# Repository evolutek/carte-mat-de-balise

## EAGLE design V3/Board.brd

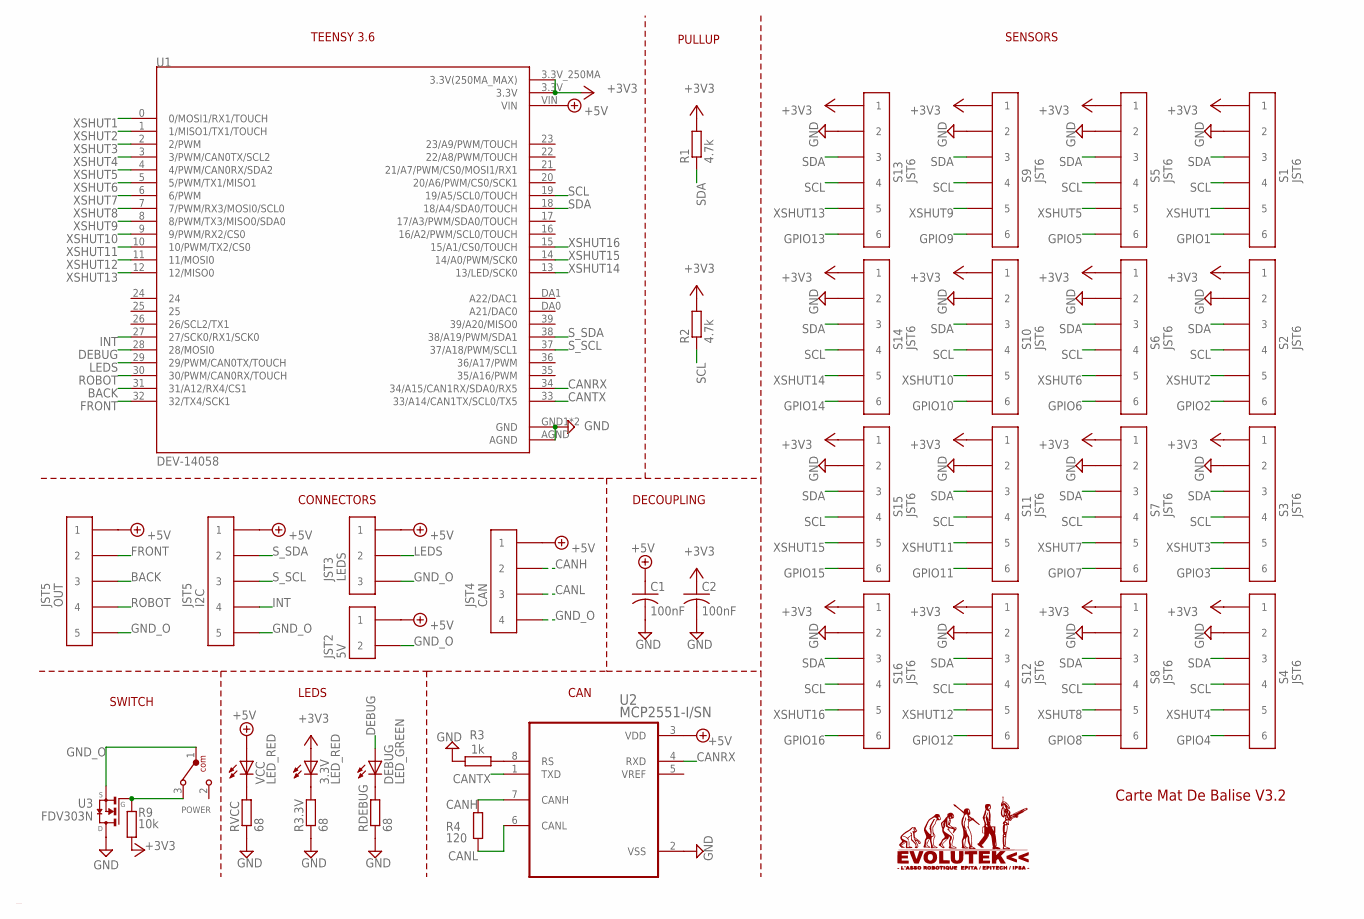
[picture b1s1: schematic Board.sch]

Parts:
3.3V: LED_RED; CHIPLED_0805
5V: JST2; B02B-PASK
C1, C2: 100nF; C0603
CAN: JST4; B04B-PASK
DEBUG: LED_GREEN; CHIPLED_0805
I2C: JST5; B05B-PASK
LEDS: JST3; B03B-PASK
OUT: JST5; B05B-PASK
POWER: 450302014072
R1, R2: 4.7k; R0603
R3: 1k; R0603
R3.3V: 68; R0603
R4: 120; R0603
R9: 10k; R0603
RDEBUG: 68; R0603
RVCC: 68; R0603
S1, S2, S3, S4, S5, S6, S7, S8, S9, S10, S11, S12, S13, S14, S15, S16: JST6; B06B-PASK
U1: DEV-14058; MODULE_DEV-14058
U2: MCP2551-I/SN; SOIC127P599X175-8N
U3: FDV303N; SOT23
VCC: LED_RED; CHIPLED_0805

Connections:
+3V3: 3.3V.A, C2.1, R1.2, R2.2, R9.2, S1.P$1 (1), S2.P$1 (1), S3.P$1 (1), S4.P$1 (1), S5.P$1 (1), S6.P$1 (1), S7.P$1 (1), S8.P$1 (1), S9.P$1 (1), S10.P$1 (1), S11.P$1 (1), S12.P$1 (1), S13.P$1 (1), S14.P$1 (1), S15.P$1 (1), S16.P$1 (1), U1.3.3V, U1.3.3V_250MA (3.3V(250MA_MAX))
+5V: 5V.P$1 (1), C1.1, CAN.P$1 (1), I2C.P$1 (1), LEDS.P$1 (1), OUT.P$1 (1), U1.VIN, U2.3 (VDD), VCC.A
BACK: OUT.P$3 (3), U1.31 (31/A12/RX4/CS1)
CANH: CAN.P$2 (2), R4.1, U2.7 (CANH)
CANL: CAN.P$3 (3), R4.2, U2.6 (CANL)
CANRX: U1.34 (34/A15/CAN1RX/SDA0/RX5), U2.4 (RXD)
CANTX: U1.33 (33/A14/CAN1TX/SCL0/TX5), U2.1 (TXD)
DEBUG: DEBUG.A, U1.28 (28/MOSI0)
FRONT: OUT.P$2 (2), U1.32 (32/TX4/SCK1)
GND: C1.2, C2.2, R3.2, R3.3V.1, RDEBUG.1, RVCC.1, S1.P$2 (2), S2.P$2 (2), S3.P$2 (2), S4.P$2 (2), S5.P$2 (2), S6.P$2 (2), S7.P$2 (2), S8.P$2 (2), S9.P$2 (2), S10.P$2 (2), S11.P$2 (2), S12.P$2 (2), S13.P$2 (2), S14.P$2 (2), S15.P$2 (2), S16.P$2 (2), U1.AGND, U1.GND1 (GND), U1.GND2 (GND), U2.2 (VSS), U3.3 (D)
GND_O: 5V.P$2 (2), CAN.P$4 (4), I2C.P$5 (5), LEDS.P$3 (3), OUT.P$5 (5), POWER.1, U3.2 (S)
GPIO1: S1.P$6 (6)
GPIO2: S2.P$6 (6)
GPIO3: S3.P$6 (6)
GPIO4: S4.P$6 (6)
GPIO5: S5.P$6 (6)
GPIO6: S6.P$6 (6)
GPIO7: S7.P$6 (6)
GPIO8: S8.P$6 (6)
GPIO9: S9.P$6 (6)
GPIO10: S10.P$6 (6)
GPIO11: S11.P$6 (6)
GPIO12: S12.P$6 (6)
GPIO13: S13.P$6 (6)
GPIO14: S14.P$6 (6)
GPIO15: S15.P$6 (6)
GPIO16: S16.P$6 (6)
INT: I2C.P$4 (4), U1.27 (27/SCK0/RX1/SCK0)
LEDS: LEDS.P$2 (2), U1.29 (29/PWM/CAN0TX/TOUCH)
unnamed: 3.3V.C, R3.3V.2
unnamed: DEBUG.C, RDEBUG.2
unnamed: R3.1, U2.8 (RS)
unnamed: RVCC.2, VCC.C
unnamed: POWER.3, R9.1, U3.1 (G)
ROBOT: OUT.P$4 (4), U1.30 (30/PWM/CAN0RX/TOUCH)
SCL: R2.1, S1.P$4 (4), S2.P$4 (4), S3.P$4 (4), S4.P$4 (4), S5.P$4 (4), S6.P$4 (4), S7.P$4 (4), S8.P$4 (4), S9.P$4 (4), S10.P$4 (4), S11.P$4 (4), S12.P$4 (4), S13.P$4 (4), S14.P$4 (4), S15.P$4 (4), S16.P$4 (4), U1.19 (19/A5/SCL0/TOUCH)
SDA: R1.1, S1.P$3 (3), S2.P$3 (3), S3.P$3 (3), S4.P$3 (3), S5.P$3 (3), S6.P$3 (3), S7.P$3 (3), S8.P$3 (3), S9.P$3 (3), S10.P$3 (3), S11.P$3 (3), S12.P$3 (3), S13.P$3 (3), S14.P$3 (3), S15.P$3 (3), S16.P$3 (3), U1.18 (18/A4/SDA0/TOUCH)
S_SCL: I2C.P$3 (3), U1.37 (37/A18/PWM/SCL1)
S_SDA: I2C.P$2 (2), U1.38 (38/A19/PWM/SDA1)
XSHUT1: S1.P$5 (5), U1.0 (0/MOSI1/RX1/TOUCH)
XSHUT2: S2.P$5 (5), U1.1 (1/MISO1/TX1/TOUCH)
XSHUT3: S3.P$5 (5), U1.2 (2/PWM)
XSHUT4: S4.P$5 (5), U1.3 (3/PWM/CAN0TX/SCL2)
XSHUT5: S5.P$5 (5), U1.4 (4/PWM/CAN0RX/SDA2)
XSHUT6: S6.P$5 (5), U1.5 (5/PWM/TX1/MISO1)
XSHUT7: S7.P$5 (5), U1.6 (6/PWM)
XSHUT8: S8.P$5 (5), U1.7 (7/PWM/RX3/MOSI0/SCL0)
XSHUT9: S9.P$5 (5), U1.8 (8/PWM/TX3/MISO0/SDA0)
XSHUT10: S10.P$5 (5), U1.9 (9/PWM/RX2/CS0)
XSHUT11: S11.P$5 (5), U1.10 (10/PWM/TX2/CS0)
XSHUT12: S12.P$5 (5), U1.11 (11/MOSI0)
XSHUT13: S13.P$5 (5), U1.12 (12/MISO0)
XSHUT14: S14.P$5 (5), U1.13 (13/LED/SCK0)
XSHUT15: S15.P$5 (5), U1.14 (14/A0/PWM/SCK0)
XSHUT16: S16.P$5 (5), U1.15 (15/A1/CS0/TOUCH)

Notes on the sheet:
SENSORS
TEENSY 3.6
CONNECTORS
SWITCH
DECOUPLING
LEDS
PULLUP
CAN
C:/Users/coren/Documents/MEGA/logo_evo.bmp
Carte Mat De Balise V3.2

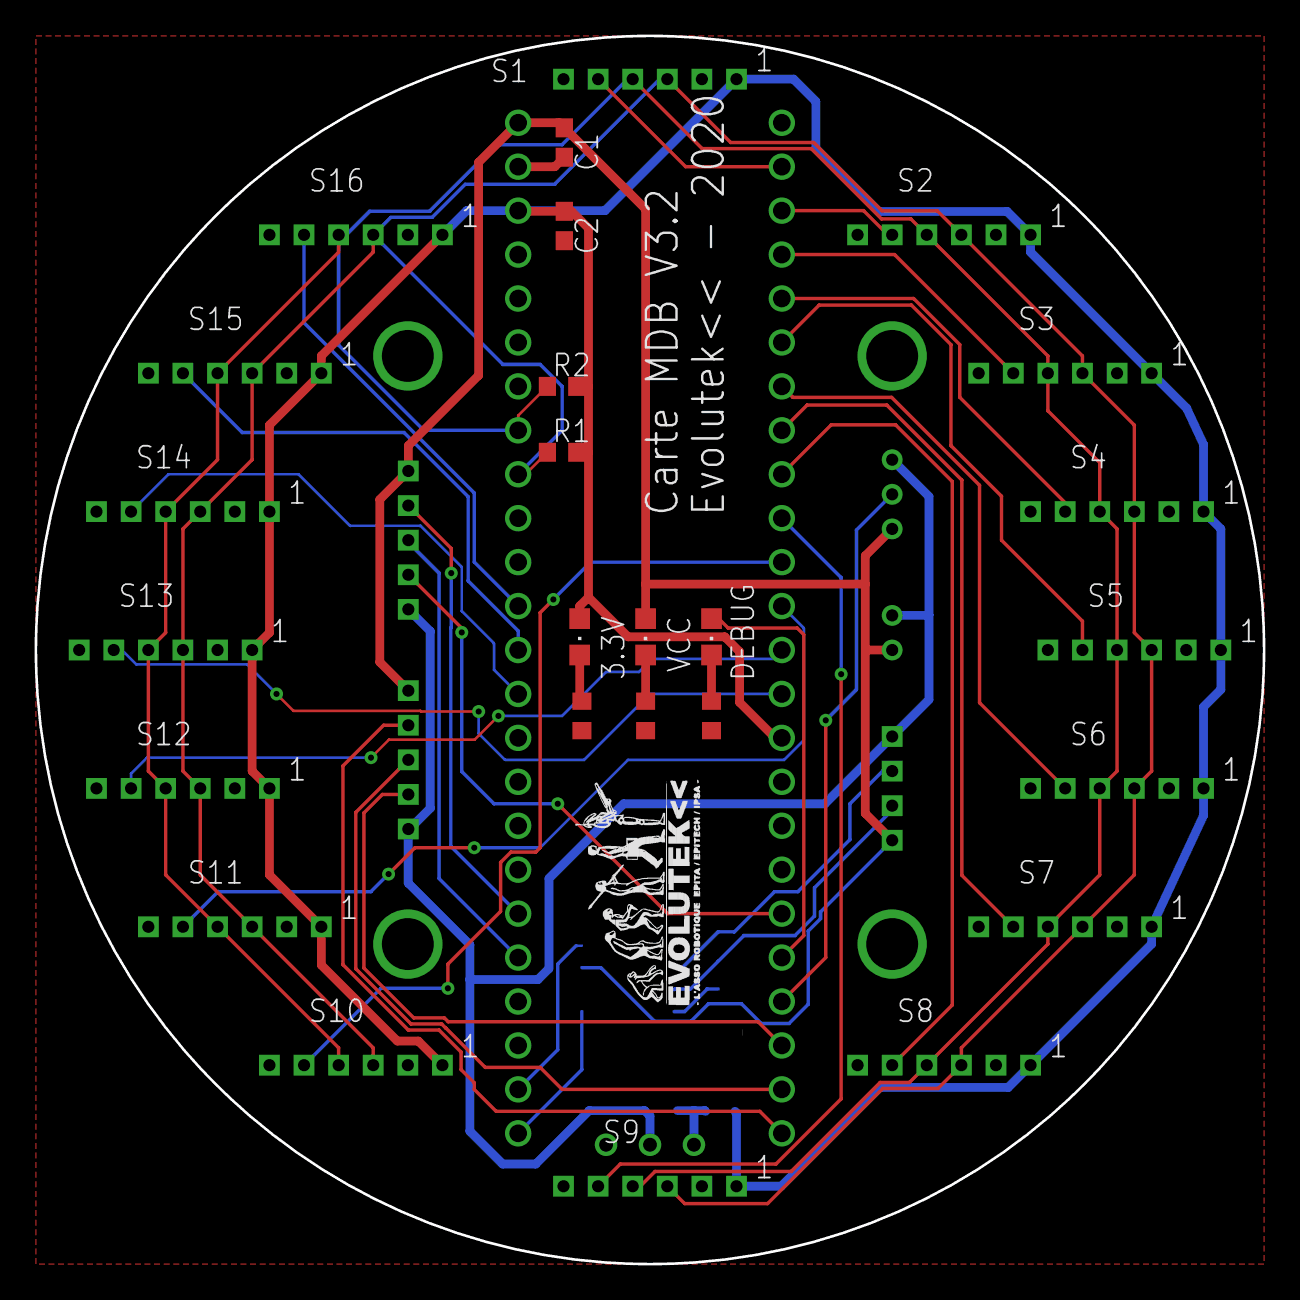
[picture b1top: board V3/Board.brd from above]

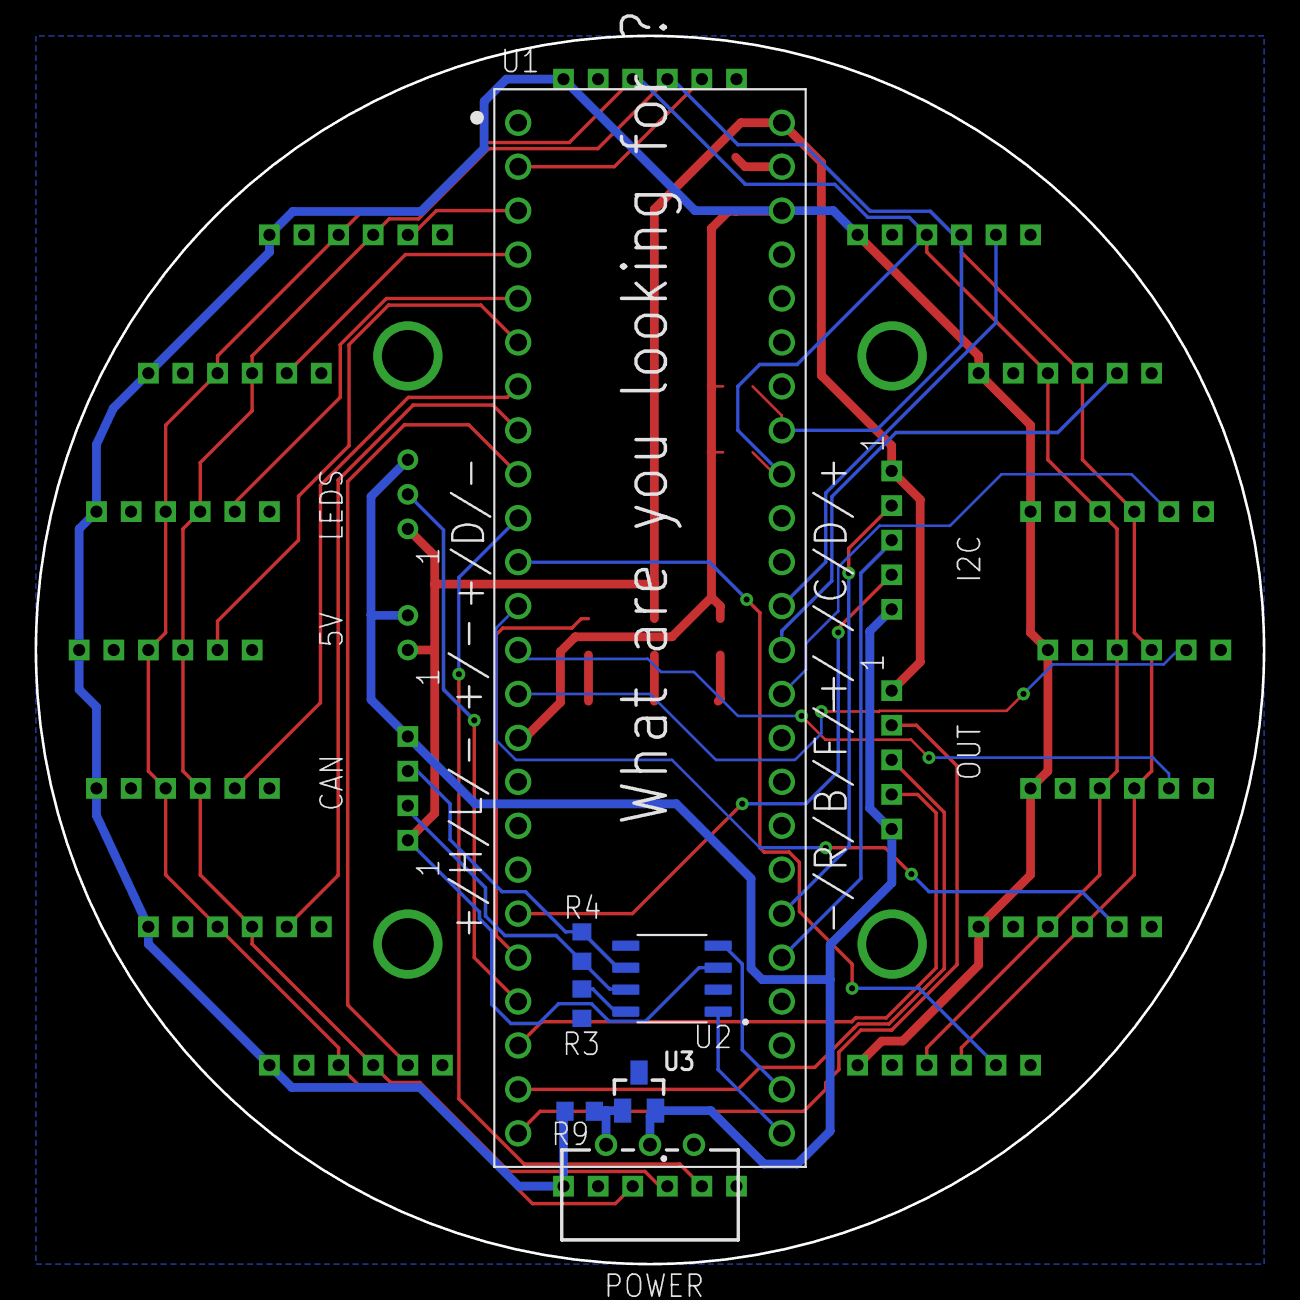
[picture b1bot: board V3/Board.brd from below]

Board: 2 copper layers, 71.0 x 71.0 mm, 38 parts (12 on the bottom side), 39 nets.

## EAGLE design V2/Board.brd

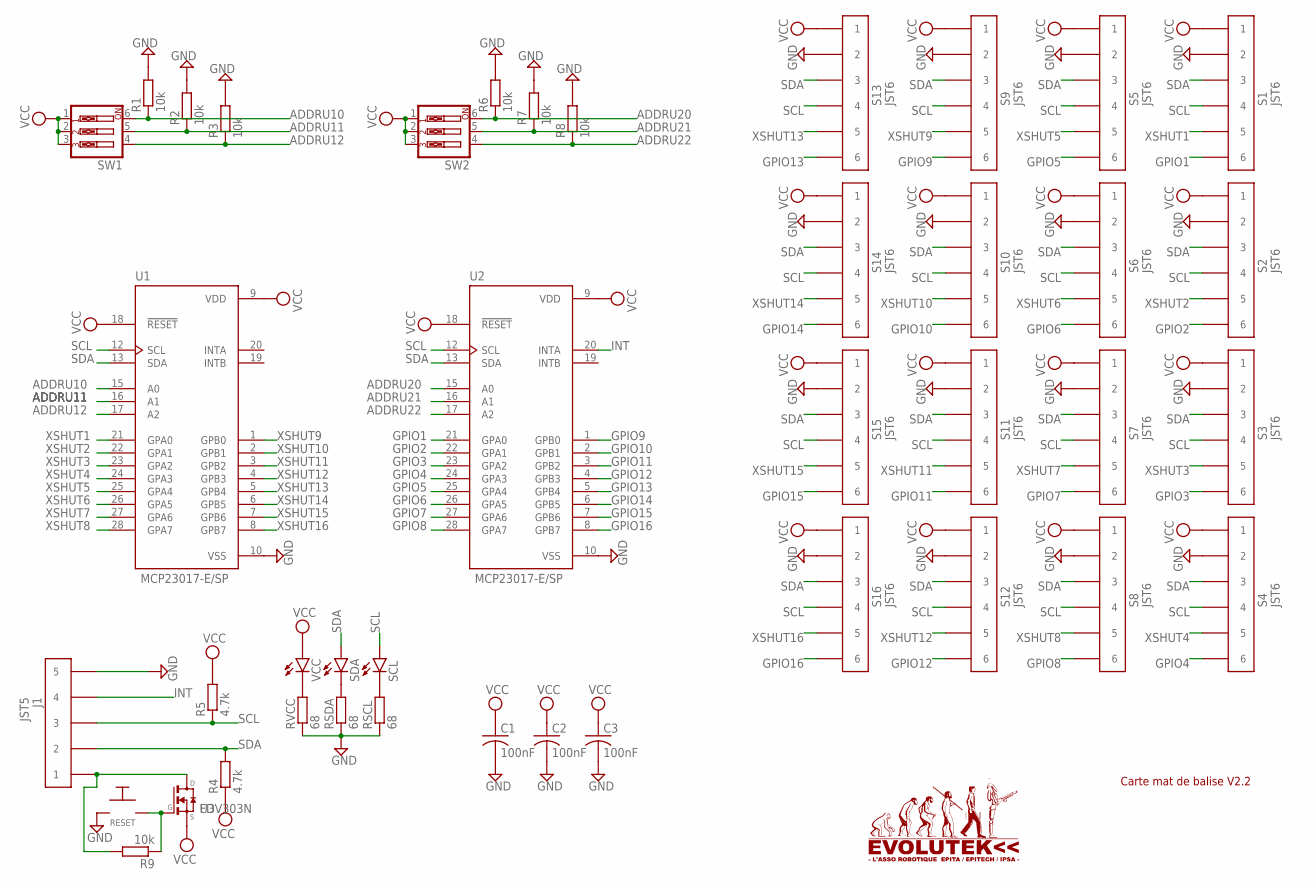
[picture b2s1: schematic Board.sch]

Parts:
C1, C2, C3: 100nF; C0603
J1: JST5; B05B-PASK
R1, R2, R3, R6, R7, R8, R9: 10k; R0603
R4, R5: 4.7k; R0603
RESET: 1825095-3
RSCL: 68; R0603
RSDA: 68; R0603
RVCC: 68; R0603
S1, S2, S3, S4, S5, S6, S7, S8, S9, S10, S11, S12, S13, S14, S15, S16: JST6; B06B-PASK
SCL: LEDCHIPLED_0805; CHIPLED_0805
SDA: LEDCHIPLED_0805; CHIPLED_0805
SW1, SW2: SW_DIP-3; EDG-03
U1, U2: MCP23017-E/SP; DIP787W45P254L3556H508Q28
U3: FDV303N; SOT23
VCC: LEDCHIPLED_0805; CHIPLED_0805

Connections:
ADDRU10: R1.1, SW1.6, U1.15 (A0)
ADDRU11: R2.1, SW1.5, U1.16 (A1)
ADDRU12: R3.1, SW1.4, U1.17 (A2)
ADDRU20: R6.1, SW2.6, U2.15 (A0)
ADDRU21: R7.1, SW2.5, U2.16 (A1)
ADDRU22: R8.1, SW2.4, U2.17 (A2)
GND: C1.2, C2.2, C3.2, J1.P$5 (5), R1.2, R2.2, R3.2, R6.2, R7.2, R8.2, RESET.P$3, RSCL.1, RSDA.1, RVCC.1, S1.P$2 (2), S2.P$2 (2), S3.P$2 (2), S4.P$2 (2), S5.P$2 (2), S6.P$2 (2), S7.P$2 (2), S8.P$2 (2), S9.P$2 (2), S10.P$2 (2), S11.P$2 (2), S12.P$2 (2), S13.P$2 (2), S14.P$2 (2), S15.P$2 (2), S16.P$2 (2), U1.10 (VSS), U2.10 (VSS)
GPIO1: S1.P$6 (6), U2.21 (GPA0)
GPIO2: S2.P$6 (6), U2.22 (GPA1)
GPIO3: S3.P$6 (6), U2.23 (GPA2)
GPIO4: S4.P$6 (6), U2.24 (GPA3)
GPIO5: S5.P$6 (6), U2.25 (GPA4)
GPIO6: S6.P$6 (6), U2.26 (GPA5)
GPIO7: S7.P$6 (6), U2.27 (GPA6)
GPIO8: S8.P$6 (6), U2.28 (GPA7)
GPIO9: S9.P$6 (6), U2.1 (GPB0)
GPIO10: S10.P$6 (6), U2.2 (GPB1)
GPIO11: S11.P$6 (6), U2.3 (GPB2)
GPIO12: S12.P$6 (6), U2.4 (GPB3)
GPIO13: S13.P$6 (6), U2.5 (GPB4)
GPIO14: S14.P$6 (6), U2.6 (GPB5)
GPIO15: S15.P$6 (6), U2.7 (GPB6)
GPIO16: S16.P$6 (6), U2.8 (GPB7)
INT: J1.P$4 (4), U2.20 (INTA)
unnamed: R9.1, RESET.P$1, U3.1 (G)
unnamed: J1.P$1 (1), R9.2, U3.3 (D)
unnamed: RSDA.2, SDA.C
unnamed: RSCL.2, SCL.C
unnamed: RVCC.2, VCC.C
SCL: J1.P$3 (3), R5.1, S1.P$4 (4), S2.P$4 (4), S3.P$4 (4), S4.P$4 (4), S5.P$4 (4), S6.P$4 (4), S7.P$4 (4), S8.P$4 (4), S9.P$4 (4), S10.P$4 (4), S11.P$4 (4), S12.P$4 (4), S13.P$4 (4), S14.P$4 (4), S15.P$4 (4), S16.P$4 (4), SCL.A, U1.12 (SCL), U2.12 (SCL)
SDA: J1.P$2 (2), R4.2, S1.P$3 (3), S2.P$3 (3), S3.P$3 (3), S4.P$3 (3), S5.P$3 (3), S6.P$3 (3), S7.P$3 (3), S8.P$3 (3), S9.P$3 (3), S10.P$3 (3), S11.P$3 (3), S12.P$3 (3), S13.P$3 (3), S14.P$3 (3), S15.P$3 (3), S16.P$3 (3), SDA.A, U1.13 (SDA), U2.13 (SDA)
VCC: C1.1, C2.1, C3.1, R4.1, R5.2, S1.P$1 (1), S2.P$1 (1), S3.P$1 (1), S4.P$1 (1), S5.P$1 (1), S6.P$1 (1), S7.P$1 (1), S8.P$1 (1), S9.P$1 (1), S10.P$1 (1), S11.P$1 (1), S12.P$1 (1), S13.P$1 (1), S14.P$1 (1), S15.P$1 (1), S16.P$1 (1), SW1.1, SW1.2, SW1.3, SW2.1, SW2.2, SW2.3, U1.9 (VDD), U1.18 (!RESET), U2.9 (VDD), U2.18 (!RESET), U3.2 (S), VCC.A
XSHUT1: S1.P$5 (5), U1.21 (GPA0)
XSHUT2: S2.P$5 (5), U1.22 (GPA1)
XSHUT3: S3.P$5 (5), U1.23 (GPA2)
XSHUT4: S4.P$5 (5), U1.24 (GPA3)
XSHUT5: S5.P$5 (5), U1.25 (GPA4)
XSHUT6: S6.P$5 (5), U1.26 (GPA5)
XSHUT7: S7.P$5 (5), U1.27 (GPA6)
XSHUT8: S8.P$5 (5), U1.28 (GPA7)
XSHUT9: S9.P$5 (5), U1.1 (GPB0)
XSHUT10: S10.P$5 (5), U1.2 (GPB1)
XSHUT11: S11.P$5 (5), U1.3 (GPB2)
XSHUT12: S12.P$5 (5), U1.4 (GPB3)
XSHUT13: S13.P$5 (5), U1.5 (GPB4)
XSHUT14: S14.P$5 (5), U1.6 (GPB5)
XSHUT15: S15.P$5 (5), U1.7 (GPB6)
XSHUT16: S16.P$5 (5), U1.8 (GPB7)

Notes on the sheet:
Carte mat de balise V2.2

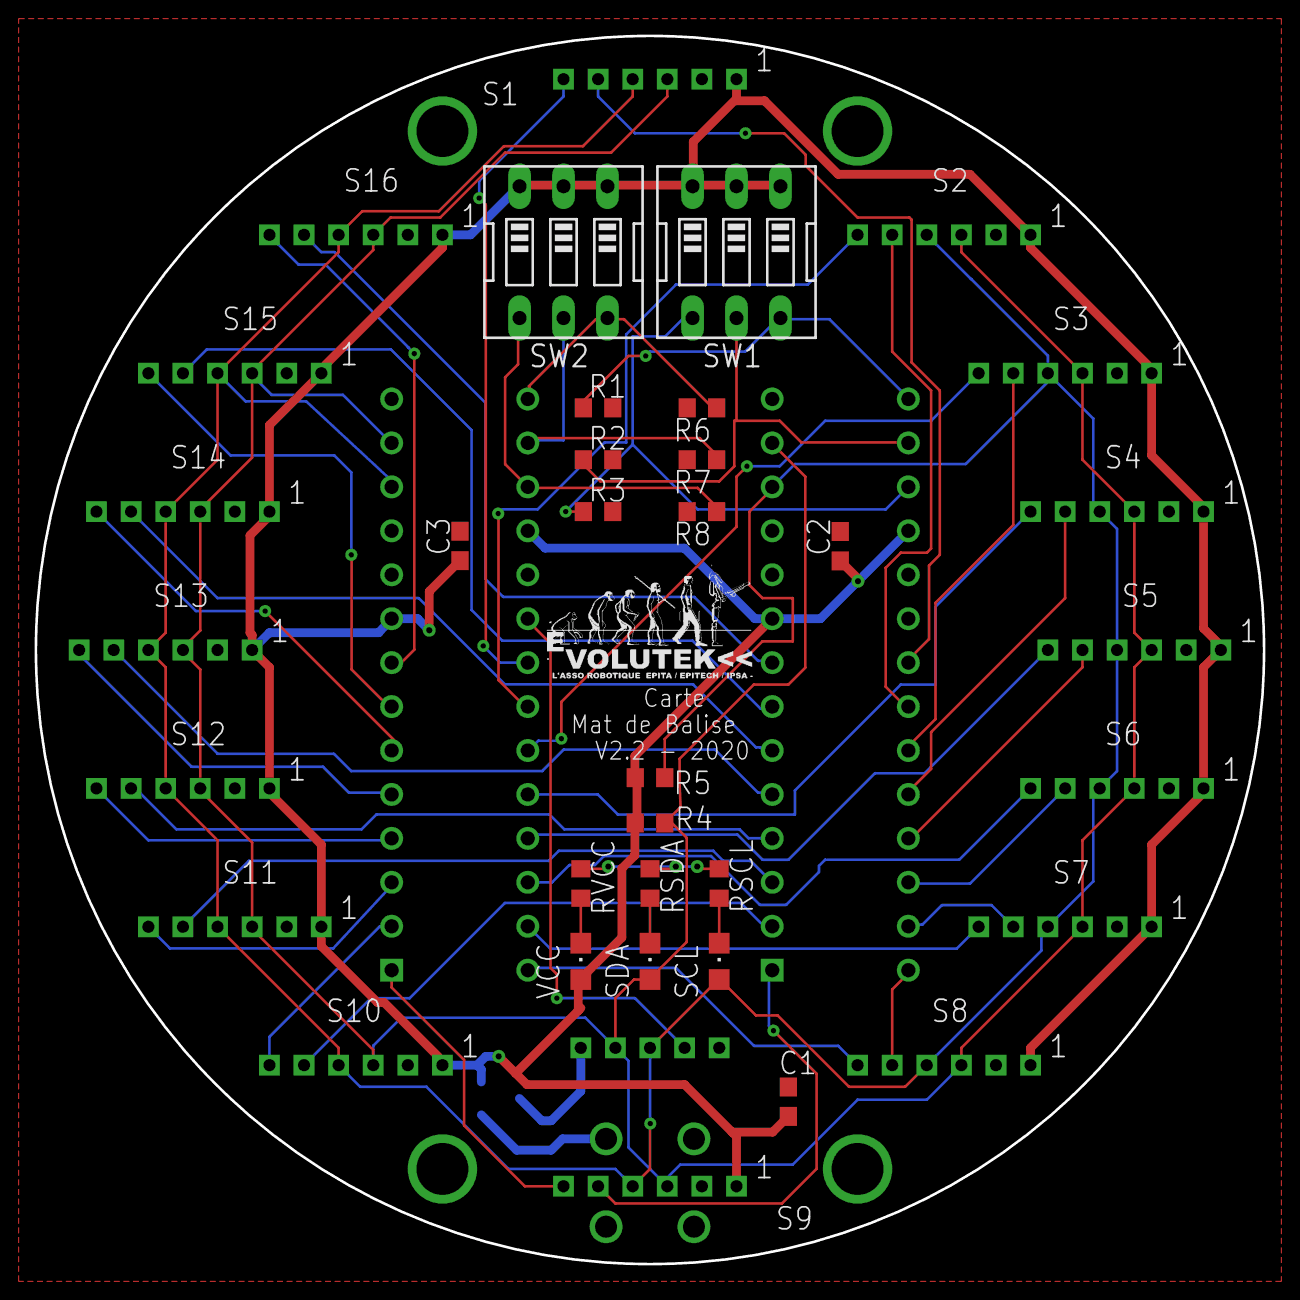
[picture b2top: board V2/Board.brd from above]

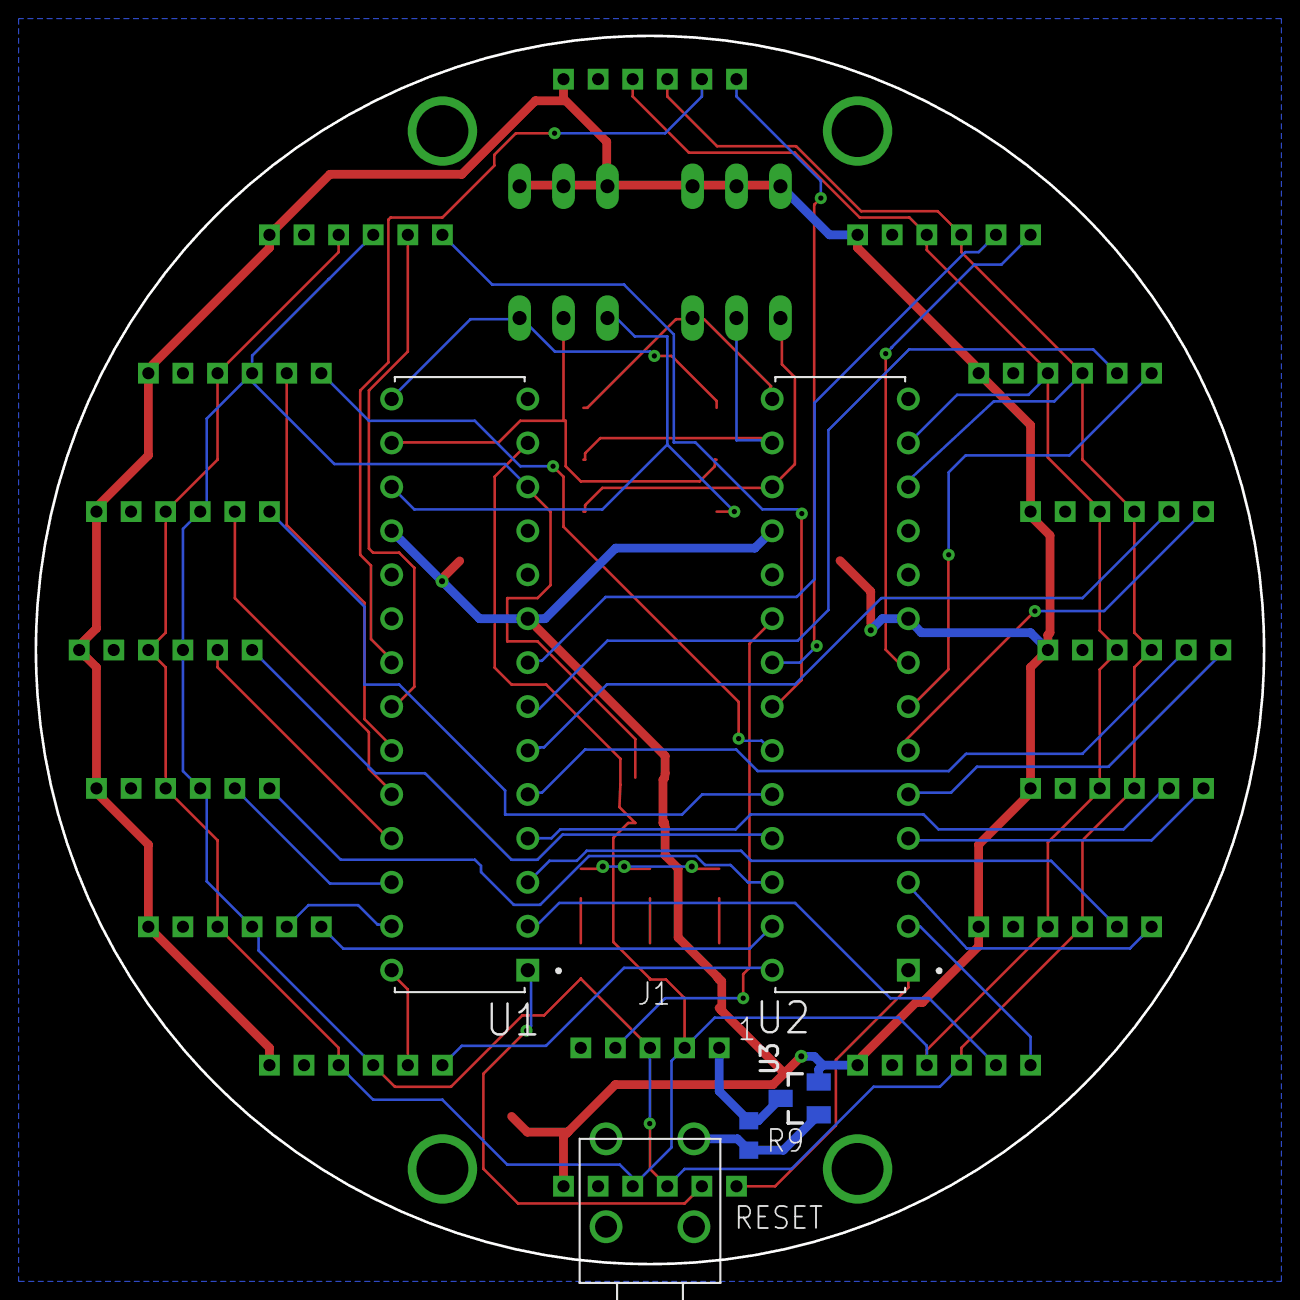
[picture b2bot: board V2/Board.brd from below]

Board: 2 copper layers, 71.0 x 71.0 mm, 41 parts (6 on the bottom side), 48 nets.

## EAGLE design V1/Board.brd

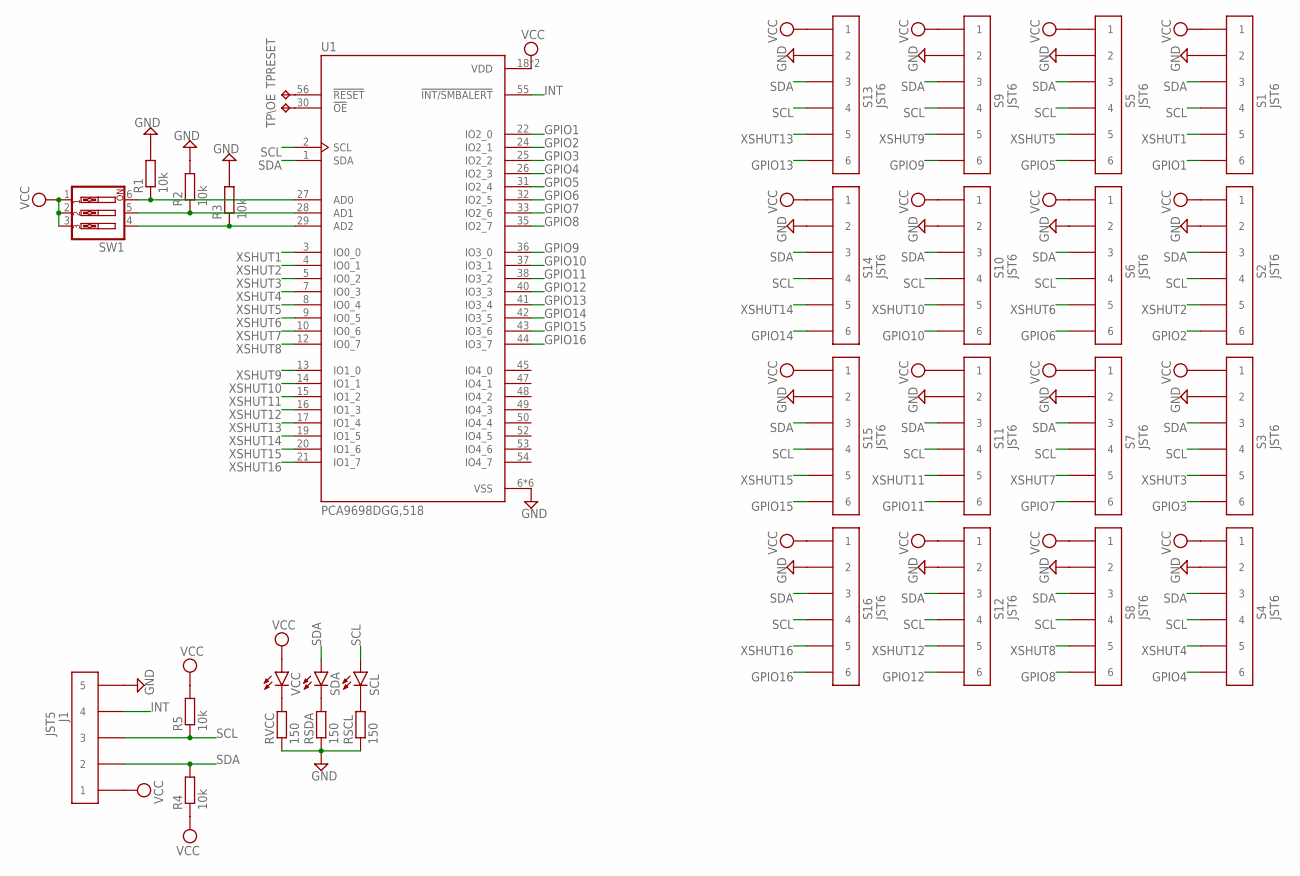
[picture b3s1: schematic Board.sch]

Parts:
J1: JST5; B05B-PASK
R1, R2, R3, R4, R5: 10k; R0603
RSCL: 150; R0603
RSDA: 150; R0603
RVCC: 150; R0603
S1, S2, S3, S4, S5, S6, S7, S8, S9, S10, S11, S12, S13, S14, S15, S16: JST6; B06B-PASK
SCL: LEDCHIPLED_0805; CHIPLED_0805
SDA: LEDCHIPLED_0805; CHIPLED_0805
SW1: SW_DIP-3; EDG-03
TPRESET: TPPAD1-13; P1-13
TP\OE: TPPAD1-13; P1-13
U1: PCA9698DGG,518; SOP50P810X120-56N
VCC: LEDCHIPLED_0805; CHIPLED_0805

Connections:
GND: J1.P$5 (5), R1.2, R2.2, R3.2, RSCL.1, RSDA.1, RVCC.1, S1.P$2 (2), S2.P$2 (2), S3.P$2 (2), S4.P$2 (2), S5.P$2 (2), S6.P$2 (2), S7.P$2 (2), S8.P$2 (2), S9.P$2 (2), S10.P$2 (2), S11.P$2 (2), S12.P$2 (2), S13.P$2 (2), S14.P$2 (2), S15.P$2 (2), S16.P$2 (2), U1.6 (VSS), U1.11 (VSS), U1.23 (VSS), U1.34 (VSS), U1.39 (VSS), U1.51 (VSS)
GPIO1: S1.P$6 (6), U1.22 (IO2_0)
GPIO2: S2.P$6 (6), U1.24 (IO2_1)
GPIO3: S3.P$6 (6), U1.25 (IO2_2)
GPIO4: S4.P$6 (6), U1.26 (IO2_3)
GPIO5: S5.P$6 (6), U1.31 (IO2_4)
GPIO6: S6.P$6 (6), U1.32 (IO2_5)
GPIO7: S7.P$6 (6), U1.33 (IO2_6)
GPIO8: S8.P$6 (6), U1.35 (IO2_7)
GPIO9: S9.P$6 (6), U1.36 (IO3_0)
GPIO10: S10.P$6 (6), U1.37 (IO3_1)
GPIO11: S11.P$6 (6), U1.38 (IO3_2)
GPIO12: S12.P$6 (6), U1.40 (IO3_3)
GPIO13: S13.P$6 (6), U1.41 (IO3_4)
GPIO14: S14.P$6 (6), U1.42 (IO3_5)
GPIO15: S15.P$6 (6), U1.43 (IO3_6)
GPIO16: S16.P$6 (6), U1.44 (IO3_7)
INT: J1.P$4 (4), U1.55 (!INT/SMBALERT)
unnamed: TPRESET.TP, U1.56 (!RESET)
unnamed: R3.1, SW1.4, U1.29 (AD2)
unnamed: R2.1, SW1.5, U1.28 (AD1)
unnamed: R1.1, SW1.6, U1.27 (AD0)
unnamed: TP\OE.TP, U1.30 (!OE)
unnamed: RSDA.2, SDA.C
unnamed: RSCL.2, SCL.C
unnamed: RVCC.2, VCC.C
SCL: J1.P$3 (3), R5.1, S1.P$4 (4), S2.P$4 (4), S3.P$4 (4), S4.P$4 (4), S5.P$4 (4), S6.P$4 (4), S7.P$4 (4), S8.P$4 (4), S9.P$4 (4), S10.P$4 (4), S11.P$4 (4), S12.P$4 (4), S13.P$4 (4), S14.P$4 (4), S15.P$4 (4), S16.P$4 (4), SCL.A, U1.2 (SCL)
SDA: J1.P$2 (2), R4.2, S1.P$3 (3), S2.P$3 (3), S3.P$3 (3), S4.P$3 (3), S5.P$3 (3), S6.P$3 (3), S7.P$3 (3), S8.P$3 (3), S9.P$3 (3), S10.P$3 (3), S11.P$3 (3), S12.P$3 (3), S13.P$3 (3), S14.P$3 (3), S15.P$3 (3), S16.P$3 (3), SDA.A, U1.1 (SDA)
VCC: J1.P$1 (1), R4.1, R5.2, S1.P$1 (1), S2.P$1 (1), S3.P$1 (1), S4.P$1 (1), S5.P$1 (1), S6.P$1 (1), S7.P$1 (1), S8.P$1 (1), S9.P$1 (1), S10.P$1 (1), S11.P$1 (1), S12.P$1 (1), S13.P$1 (1), S14.P$1 (1), S15.P$1 (1), S16.P$1 (1), SW1.1, SW1.2, SW1.3, U1.18 (VDD), U1.46 (VDD), VCC.A
XSHUT1: S1.P$5 (5), U1.3 (IO0_0)
XSHUT2: S2.P$5 (5), U1.4 (IO0_1)
XSHUT3: S3.P$5 (5), U1.5 (IO0_2)
XSHUT4: S4.P$5 (5), U1.7 (IO0_3)
XSHUT5: S5.P$5 (5), U1.8 (IO0_4)
XSHUT6: S6.P$5 (5), U1.9 (IO0_5)
XSHUT7: S7.P$5 (5), U1.10 (IO0_6)
XSHUT8: S8.P$5 (5), U1.12 (IO0_7)
XSHUT9: S9.P$5 (5), U1.13 (IO1_0)
XSHUT10: S10.P$5 (5), U1.14 (IO1_1)
XSHUT11: S11.P$5 (5), U1.15 (IO1_2)
XSHUT12: S12.P$5 (5), U1.16 (IO1_3)
XSHUT13: S13.P$5 (5), U1.17 (IO1_4)
XSHUT14: S14.P$5 (5), U1.19 (IO1_5)
XSHUT15: S15.P$5 (5), U1.20 (IO1_6)
XSHUT16: S16.P$5 (5), U1.21 (IO1_7)

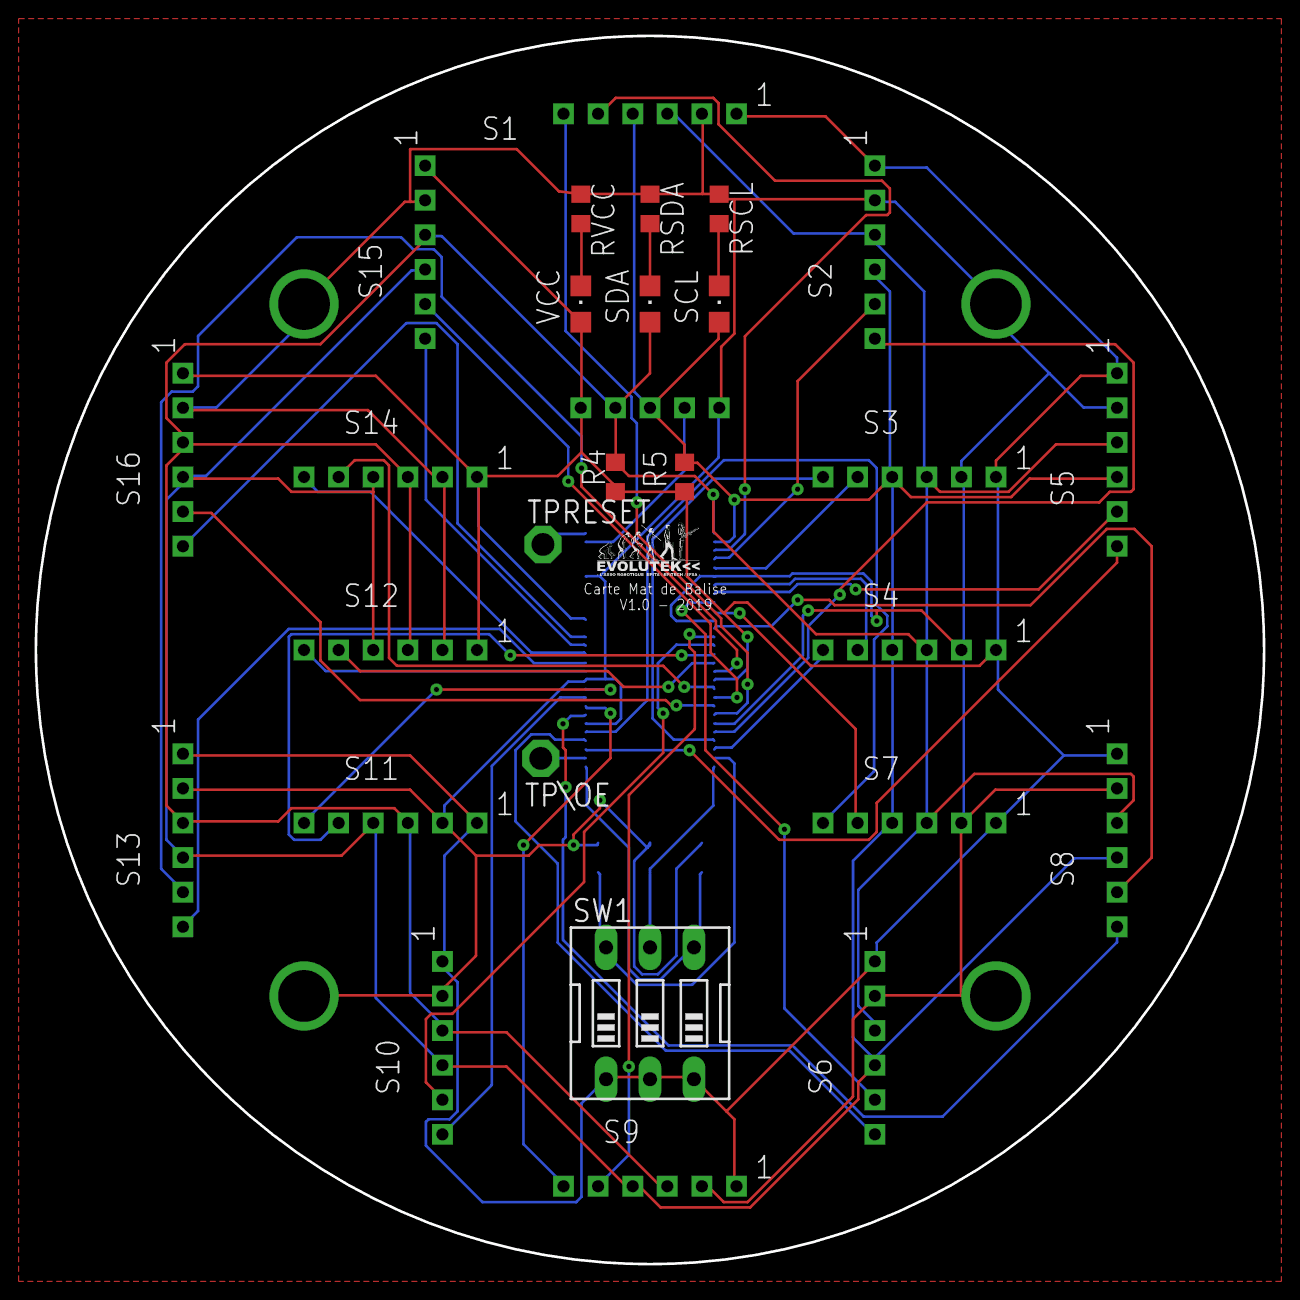
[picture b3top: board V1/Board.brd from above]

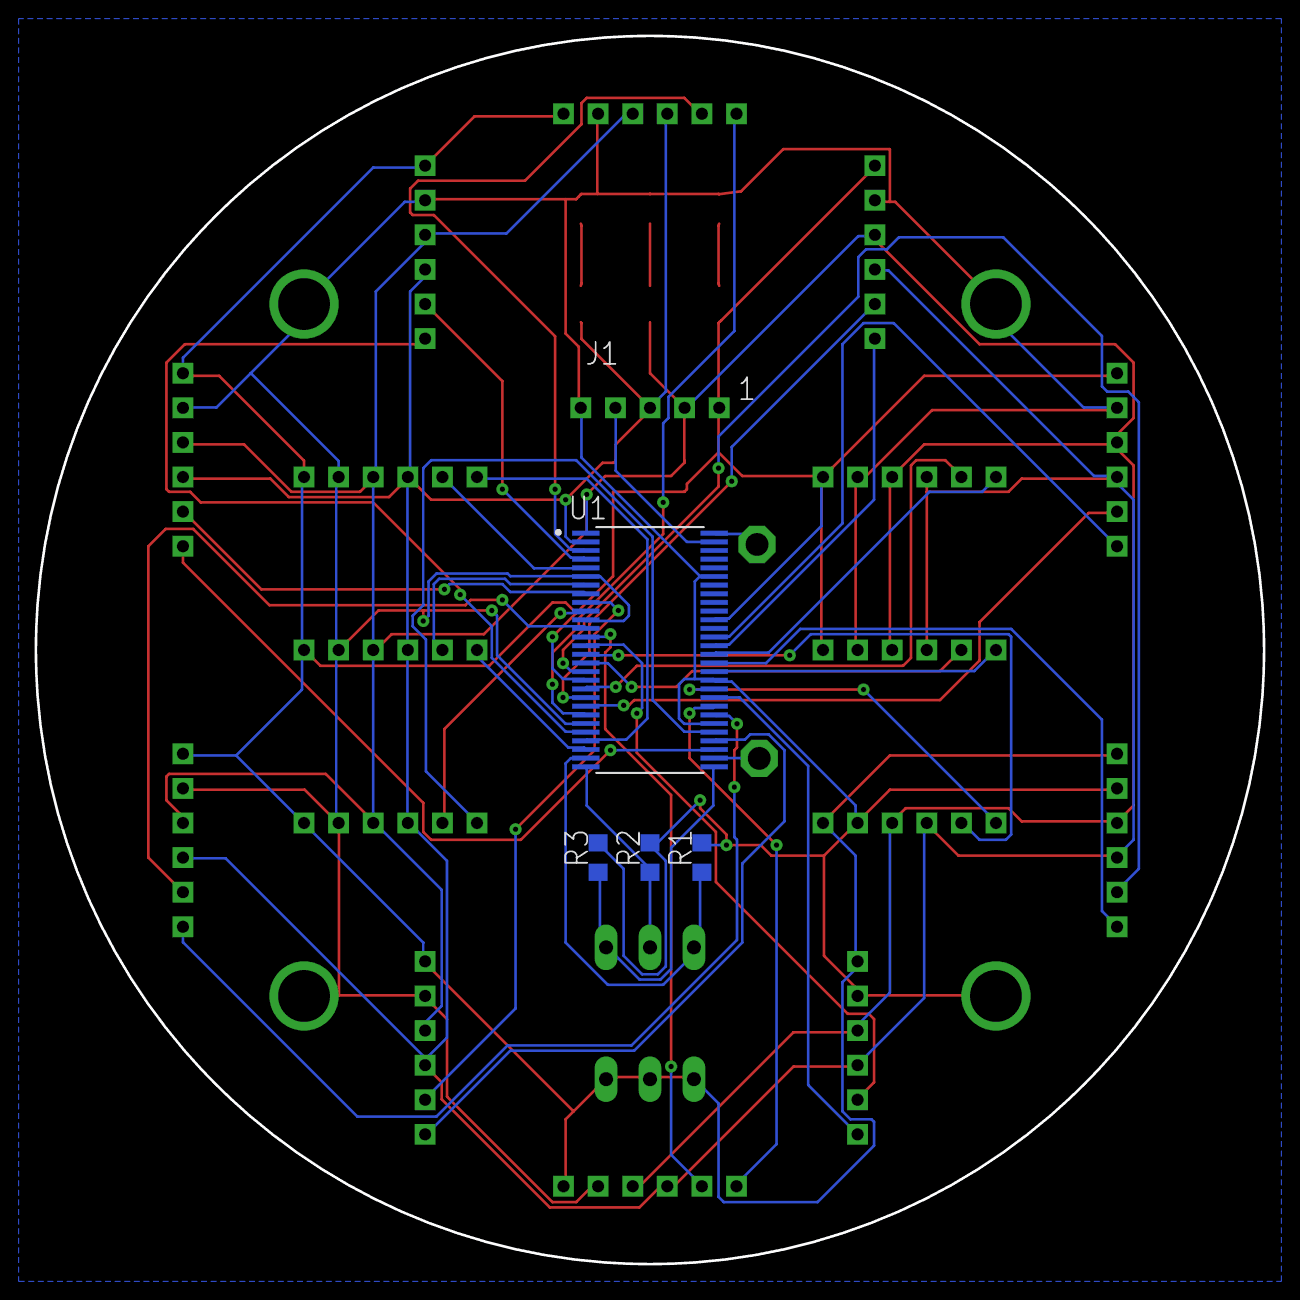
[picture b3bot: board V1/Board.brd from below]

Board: 2 copper layers, 71.0 x 71.0 mm, 32 parts (5 on the bottom side), 45 nets.

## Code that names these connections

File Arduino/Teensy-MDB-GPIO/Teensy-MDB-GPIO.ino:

#include <Wire.h>
#include <VL53L0X.h>
#include <FastLED.h>
#include <Adafruit_MCP23017.h>

// Sensors
#define AVOID_RANGE       500
#define I2C_SENSOR_SPEED  400000
#define NB_SENSORS        16
#define NB_SAMPLES        5
#define ROBOT_RANGE       1000
#define SENSOR_ADDR       0x29
#define TIMEOUT_SENSOR    500
#define XSHUT_START_GPIO  0
#define LONG_RANGE

VL53L0X sensors[NB_SENSORS];
int     scan[NB_SENSORS];
int     front_zone[]  = {15, 16, 1, 2, 3};
int     back_zone[]   = {7, 8, 9, 10, 11};
int     no_zone[]     = {4, 5, 6, 12, 13, 14};
bool    is_front    = false;
bool    is_back     = false;
bool    is_robot    = false;
int* samples[NB_SAMPLES];
int currentSample = 0;
bool enableSensors = true;

// Led strips
#define BRIGHTNESS        4
#define COLOR_ORDER       GRB
#define LED_PIN           29
#define LED_TYPE          WS2812
#define LED_LOADING_U     5
#define LED_LOADING_DELAY 100

CRGB led_loading_color = 
  //CRGB::Orange;
  CRGB::Blue;
unsigned int led_loading_next = 0;
int led_loading_current = 0;

enum debug_modes {
  DIST,
  ZONES,
  LOADING
};

enum debug_modes debug_mode = LOADING;
float   coef = 255.0 / (ROBOT_RANGE / 2);
CRGB    leds[NB_SENSORS];

// Communication
#define FRONT_GPIO        32
#define BACK_GPIO         31
#define ROBOT_GPIO        30
#define DEBUG_SERIAL

// Remove
Adafruit_MCP23017 mcp_xshut;

void init_sensor(int i) {
  #ifdef DEBUG_SERIAL
    Serial.print("Init sensor nb: ");
    Serial.println(i + 1);
  #endif

  sensors[i].init();
  sensors[i].setTimeout(TIMEOUT_SENSOR);
  sensors[i].setAddress(SENSOR_ADDR + i);

  // Enable Long Range mode
  #ifdef LONG_RANGE
    sensors[i].setSignalRateLimit(0.1);
    sensors[i].setVcselPulsePeriod(VL53L0X::VcselPeriodPreRange, 18);
    sensors[i].setVcselPulsePeriod(VL53L0X::VcselPeriodFinalRange, 14);
  #endif

  // Start continous mode
  sensors[i].startContinuous();
}


void setup() {
  // Init communication
  Wire.setClock(I2C_SENSOR_SPEED);
  Wire.begin();

  #ifdef DEBUG_SERIAL
    Serial.begin(115200);
  #endif

  pinMode(FRONT_GPIO, OUTPUT);
  digitalWrite(FRONT_GPIO, LOW);
  pinMode(BACK_GPIO, OUTPUT);
  digitalWrite(BACK_GPIO, LOW);
  pinMode(ROBOT_GPIO, OUTPUT);
  digitalWrite(ROBOT_GPIO, LOW);

  // Init Led strip
  FastLED.addLeds<LED_TYPE, LED_PIN, COLOR_ORDER>(leds, NB_SENSORS);
  FastLED.setBrightness(BRIGHTNESS);

  // Init XSHUTs
  #ifdef DEBUG_SERIAL
    Serial.println("Init XSHUTs");
  #endif

  // Remove
  mcp_xshut.begin();

  // Set every pin to output
  for (int i = 0; i < 15; ++i)
  {
    // Remove
    mcp_xshut.pinMode(i, OUTPUT);
    mcp_xshut.digitalWrite(i, LOW);

    //pinMode(XSHUT_START_GPIO + i, OUTPUT);
    //digitalWrite(XSHUT_START_GPIO + i, LOW);
    //
  }

  // Init sensors
  for (int i = NB_SENSORS -1; i >= 0; i--) {

    // Remove
    mcp_xshut.digitalWrite(i, HIGH);

    //digitalWrite(XSHUT_START_GPIO + i, HIGH);
    init_sensor(i);
  }

  for(int i = 0; i < NB_SAMPLES; i++) {
    samples[i] = (int*) malloc(sizeof(int)*NB_SENSORS);
    doSampleScan();  
  }

  if(debug_mode == LOADING)
    enableSensors = false;
}

void manage_leds() {
  
  switch(debug_mode) {
    case DIST:
      for (int i = 0; i < NB_SENSORS; i++) {
        if (scan[i] > ROBOT_RANGE)
          leds[i] = CRGB::Black;
        else {
          int r = 255 - scan[i] * coef;
          int g = 255 - abs(ROBOT_RANGE / 2 - scan[i]) * coef;
          int b = 255 - (ROBOT_RANGE - scan[i]) * coef;
          leds[i].red = r >= 0 ? r : 0;
          leds[i].green = g >= 0 ? g : 0;
          leds[i].blue = b >= 0 ? b : 0;
        }
      }
      break;

    case ZONES: 
      if(is_robot) {
        for(unsigned int i = 0; i < sizeof(leds)/sizeof(CRGB); i++)
          leds[i] = CRGB::Orange;
      } else {
        for(unsigned int i = 0; i < sizeof(leds)/sizeof(CRGB); i++)
          leds[i] = CRGB::Green;
      }   
      if(is_front) {
        for(unsigned int i = 0; i < sizeof(front_zone)/sizeof(int); i++)
          leds[front_zone[i]-1] = CRGB::Red;
      }
      if(is_back) {
        for(unsigned int i = 0; i < sizeof(back_zone)/sizeof(int); i++)
          leds[back_zone[i]-1] = CRGB::Red;
      }
      break;

    case LOADING:
      if(millis() > led_loading_next) {
        leds[led_loading_current] = CRGB::Black;
        leds[(led_loading_current + LED_LOADING_U) % NB_SENSORS] = led_loading_color;
        led_loading_current = (led_loading_current + 1) % NB_SENSORS;
        led_loading_next = millis() + LED_LOADING_DELAY;
      }
      break;

    default:
      break;
  }
   
  FastLED.show();
}

inline void updateFlags(int* _sensors, int nbSensors, bool* obstacle, bool* isRobot) {

  for (int index = 0; index < nbSensors; index++) {
    int i = _sensors[index] -1; // Index of the sensor in the sensors array
    if (obstacle && scan[i] <= AVOID_RANGE)
      *obstacle = true;
    if (scan[i] <= ROBOT_RANGE)
      *isRobot = true;
  }
}

void doSampleScan() {
  for (int sensorIndex = 0; sensorIndex < NB_SENSORS; sensorIndex++) {
      
    #ifdef DEBUG_SERIAL
      Serial.print("Sensor nb : ");
      Serial.print(sensorIndex + 1);
      Serial.print(" dist :");
    #endif

    samples[currentSample][sensorIndex] = 
      sensors[sensorIndex].readRangeContinuousMillimeters();

    #ifdef DEBUG_SERIAL
      Serial.print(samples[currentSample][sensorIndex]);
      if (sensors[sensorIndex].timeoutOccurred())
        Serial.print(" TIMEOUT");
      Serial.println();
    #endif
  }

  currentSample = (currentSample + 1)%NB_SAMPLES;
}

void loop() {

  if(!enableSensors) {
    manage_leds();
    return;
  }
  
  #ifdef DEBUG_SERIAL
    Serial.print("---- STARTING SCAN -----\n");
    int start = millis();
  #endif

  doSampleScan();

  #ifdef DEBUG_SERIAL
    Serial.print("---- END SCAN -----\n");
    Serial.print("Elapsed time: ");
    Serial.println(millis() - start);
  #endif

  for(int i = 0; i < NB_SENSORS; i++) {
    scan[i] = 0;
    #ifdef DEBUG_SERIAL
      Serial.print("Sensor id: ");
      Serial.print(i);
      Serial.print("; values:");
    #endif
    for(int j = 0; j < NB_SAMPLES; j++) {
      scan[i] += samples[j][i];
      #ifdef DEBUG_SERIAL
        Serial.print(" ");
        Serial.print(samples[j][i]);
      #endif
    }
    scan[i] /= NB_SAMPLES;
    #ifdef DEBUG_SERIAL
      Serial.print("; Average: ");
      Serial.print(scan[i]);
      Serial.println();
    #endif
  }

  bool _is_front = false;
  bool _is_back = false;
  bool _is_robot = false;

  updateFlags(front_zone, sizeof(front_zone)/sizeof(int), &_is_front, &_is_robot);
  updateFlags(back_zone, sizeof(front_zone)/sizeof(int), &_is_back, &_is_robot);
  updateFlags(no_zone, sizeof(no_zone)/sizeof(int), NULL, &_is_robot);

  is_front = _is_front;
  is_back  = _is_back;
  is_robot = _is_robot;

  digitalWrite(FRONT_GPIO, is_front);
  digitalWrite(BACK_GPIO,  is_back);
  digitalWrite(ROBOT_GPIO, is_robot);

  manage_leds();
}

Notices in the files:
parts and their libraries:
450302014072_Eagle_WS-SLTU_rev20a: Copyright: Würth Elektronik
